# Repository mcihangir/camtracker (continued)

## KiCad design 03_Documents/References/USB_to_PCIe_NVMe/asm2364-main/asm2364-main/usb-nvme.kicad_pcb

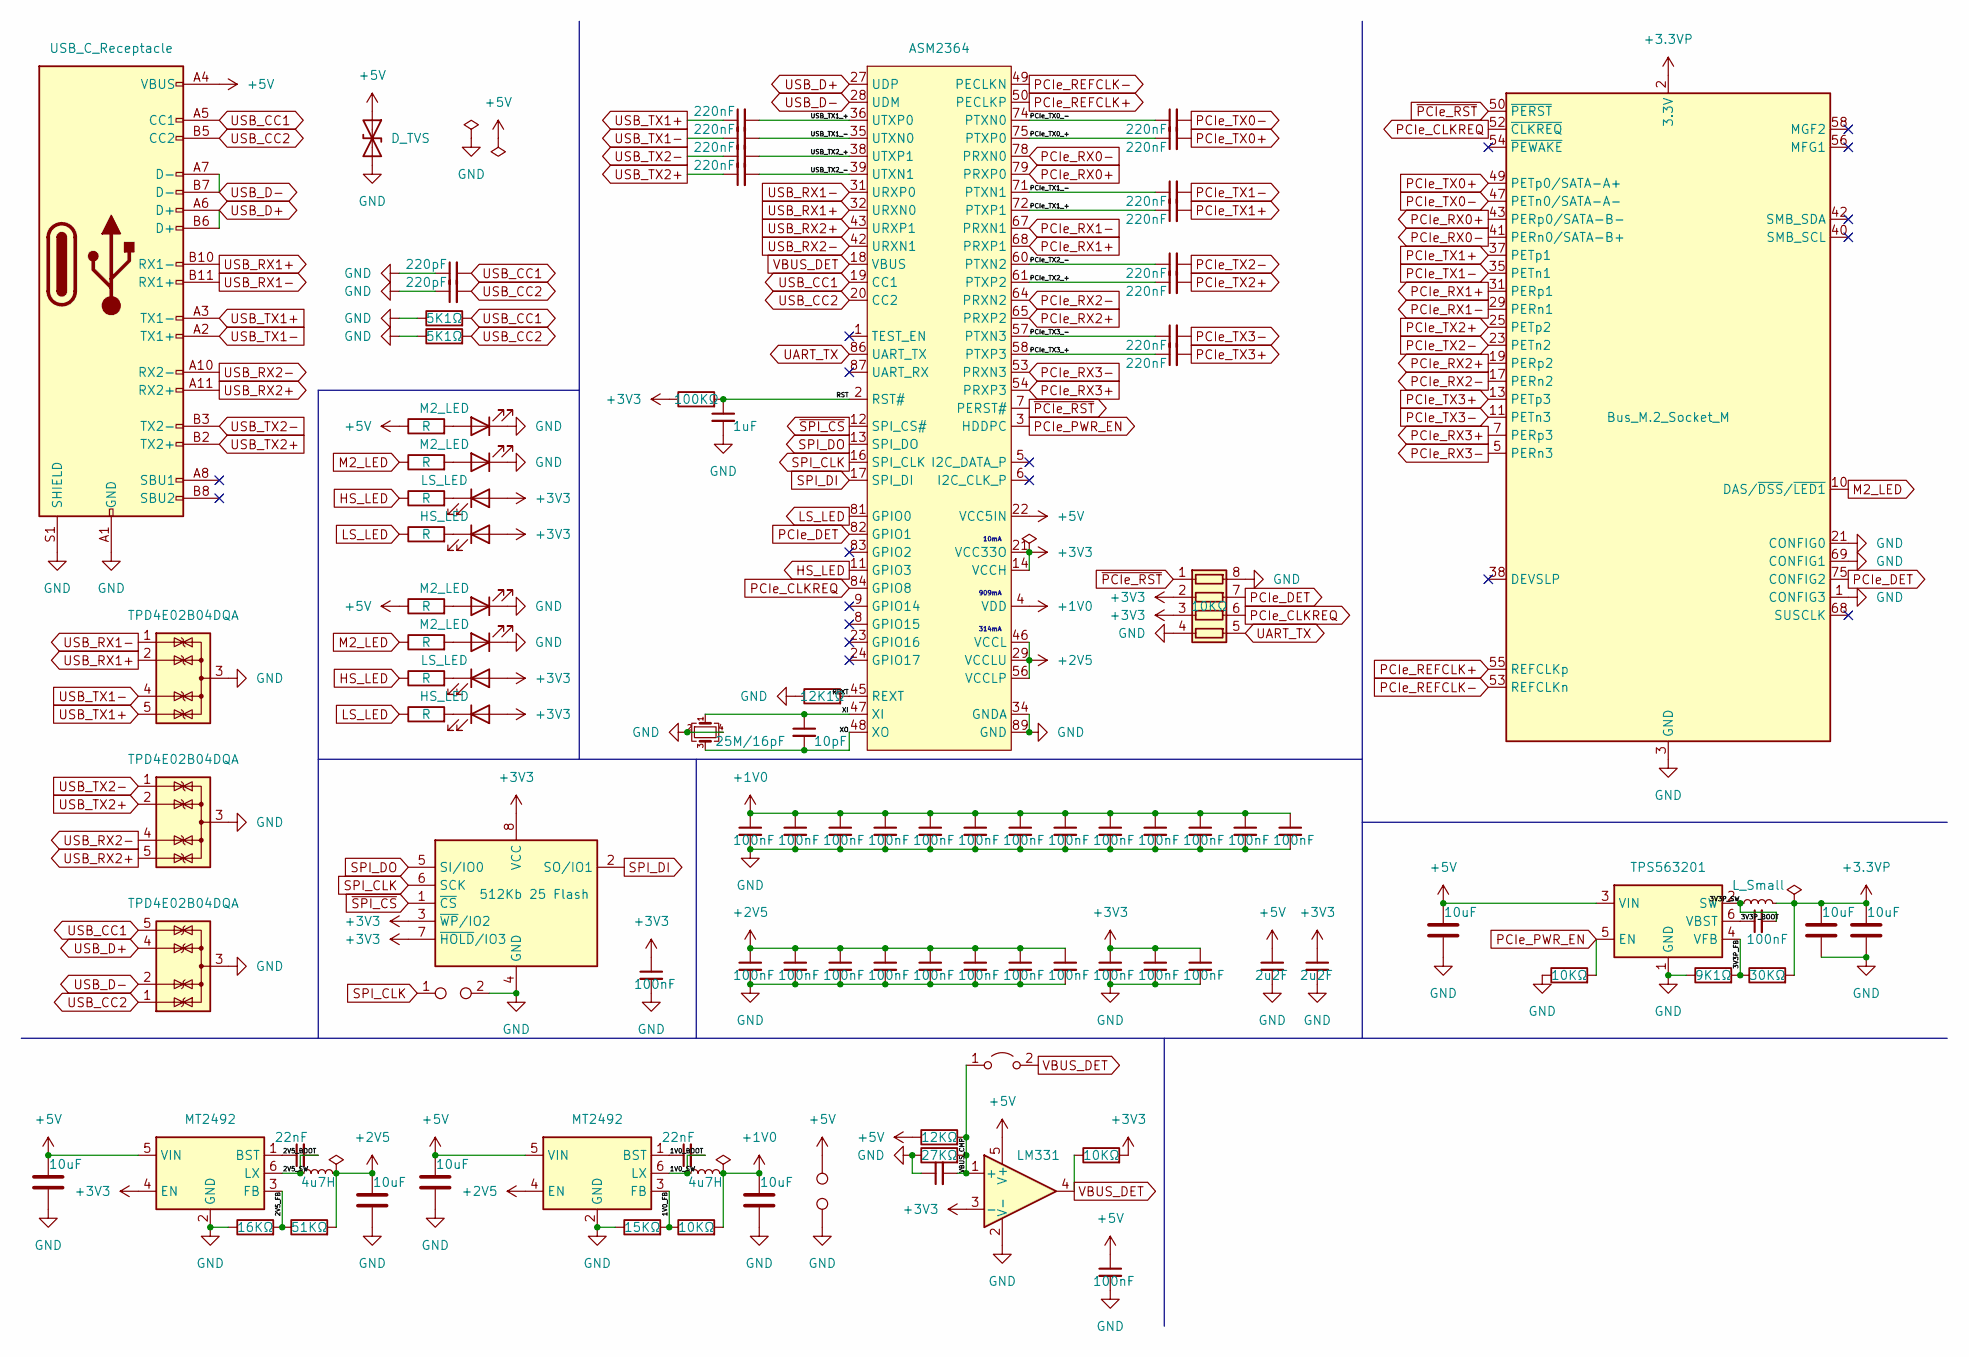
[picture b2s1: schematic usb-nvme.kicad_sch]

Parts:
C1, C2, C3, C4, C5, C6, C7, C8, C9, C11, C13, C14: 220nF; C_0201_0603Metric
C10, C12: 220pF; C_0201_0603Metric
C15: 1uF; C_0402_1005Metric
C16: 10pF; C_0201_0603Metric
C17, C18, C19, C20, C21, C22, C23, C24, C25, C26, C27, C28, C29, C30, C34, C35, C36, C37, C38, C39, C40, C41, C42, C43, C44, C47, C50, C55: 100nF; C_0201_0603Metric
C31, C32, C33, C51, C52, C53, C54: 10uF; C_0603_1608Metric
C45, C46: 2u2F; C_0402_1005Metric
C48, C49: 22nF; C_0201_0603Metric
D1: D_TVS; D_SOD-323
D2, D3, D6, D7: M2_LED; LED_0402_1005Metric
D4, D8: LS_LED; LED_0402_1005Metric
D5, D9: HS_LED; LED_0402_1005Metric
J1: USB_C_Receptacle; USB_C_Receptacle_GCT_USB4080-03-A
J2: Bus_M.2_Socket_M; M.2-M
JP1: Jumper; SolderJumper-2_1.2x0.6mm
L1: L_Small; L_Vishay_IHLP-1616
L2, L3: 4u7H; L_1008_2520Metric
R1, R2: 5K1Ω; R_0201_0603Metric
R3: 100KΩ; R_0201_0603Metric
R4, R5, R6, R7, R8, R9, R10, R12: R; R_0201_0603Metric
R11: 12K1Ω; R_0201_0603Metric
R13, R18, R22: 10KΩ; R_0201_0603Metric
R14: 9K1Ω; R_0201_0603Metric
R15: 30KΩ; R_0201_0603Metric
R16: 12KΩ; R_0201_0603Metric
R17: 27KΩ; R_0201_0603Metric
R19: 16KΩ; R_0201_0603Metric
R20: 51KΩ; R_0201_0603Metric
R21: 15KΩ; R_0201_0603Metric
RN1: 10KΩ; R_Array_Convex_4x0402
TP1: TestPoint_2Pole; R_0201_0603Metric
TP2, TP3: TestPoint; TestPoint_THTPad_2.0x2.0mm_Drill1.0mm
U1: ASM2364; QFN-88_EP_9.75x9.75_Pitch0.4mm_ThermalVias
U2, U3, U6: TPD4E02B04DQA; USON-10_2.5x1.0mm_P0.5mm
U4: 512Kb 25 Flash; DFN-8-1EP_3x2mm_P0.5mm_EP1.3x1.5mm
U5: TPS563201; SOT-23-6
U7, U8: MT2492; SOT-23-6
U9: LM331; SOT-353_SC-70-5
Y1: 25M/16pF; Crystal_SMD_2016-4Pin_2.0x1.6mm

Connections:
+1V0: C17.1, C18.1, C19.1, C20.1, C21.1, C22.1, C23.1, C24.1, C25.1, C26.1, C27.1, C28.1, C29.1, C54.1, L3.2, R22.2, U1.4 (VDD), U1.10 (VDD), U1.15 (VDD), U1.25 (VDD), U1.30 (VDD), U1.37 (VDD), U1.44 (VDD), U1.51 (VDD), U1.52 (VDD), U1.59 (VDD), U1.66 (VDD), U1.73 (VDD), U1.80 (VDD), U1.85 (VDD)
+2V5: C34.1, C35.1, C36.1, C37.1, C38.1, C39.1, C40.1, C41.1, C53.1, L2.2, R20.2, U1.29 (VCCLU), U1.33 (VCCLU), U1.41 (VCCLU), U1.46 (VCCL), U1.56 (VCCLP), U1.62 (VCCLP), U1.70 (VCCLP), U1.76 (VCCLP), U8.4 (EN)
+3.3VP: C32.1, C33.1, J2.0, J2.2 (3.3V), J2.4 (3.3V), J2.12 (3.3V), J2.14 (3.3V), J2.16 (3.3V), J2.18 (3.3V), J2.70 (3.3V), J2.72 (3.3V), J2.74 (3.3V), L1.2, R15.2
+3V3: C42.1, C43.1, C44.1, C46.1, C47.1, D4.2 (A), D5.2 (A), D8.2 (A), D9.2 (A), R3.1, R18.2, RN1.2 (R2.1), RN1.3 (R3.1), U1.14 (VCCH), U1.21 (VCC33O), U1.26 (VCCH), U1.88 (VCCH), U4.3 (~WP/IO2), U4.7 (~HOLD/IO3), U4.8 (VCC), U7.4 (EN), U9.3 (-)
+5V: C31.1, C45.1, C51.1, C52.1, C55.1, D1.1 (A1), J1.A4 (VBUS), J1.A9 (VBUS), J1.B4 (VBUS), J1.B9 (VBUS), J2.0, R4.1, R8.1, R16.1, TP2.1, U1.22 (VCC5IN), U5.3 (VIN), U7.5 (VIN), U8.5 (VIN), U9.5 (V+)
/1V0_BOOT: C49.1, U8.1 (BST)
/1V0_FB: R21.2, R22.1, U8.3 (FB)
/1V0_SW: C49.2, L3.1, U8.6 (LX)
/2V5_BOOT: C48.1, U7.1 (BST)
/2V5_FB: R19.2, R20.1, U7.3 (FB)
/2V5_SW: C48.2, L2.1, U7.6 (LX)
/3V3P_BOOT: C30.1, U5.6 (VBST)
/3V3P_FB: R14.2, R15.1, U5.4 (VFB)
/3V3P_SW: C30.2, L1.1, U5.2 (SW)
/PCIe_TX0_+: C4.1, U1.75 (PTXP0)
/PCIe_TX0_-: C2.1, U1.74 (PTXN0)
/PCIe_TX1_+: C8.1, U1.72 (PTXP1)
/PCIe_TX1_-: C7.1, U1.71 (PTXN1)
/PCIe_TX2_+: C11.1, U1.61 (PTXP2)
/PCIe_TX2_-: C9.1, U1.60 (PTXN2)
/PCIe_TX3_+: C14.1, U1.58 (PTXP3)
/PCIe_TX3_-: C13.1, U1.57 (PTXN3)
/REXT: R11.2, U1.45 (REXT)
/RST: C15.1, R3.2, U1.2 (RST#)
/USB_TX1_+: C1.2, U1.36 (UTXP0)
/USB_TX1_-: C3.2, U1.35 (UTXN0)
/USB_TX2_+: C5.2, U1.38 (UTXP1)
/USB_TX2_-: C6.2, U1.39 (UTXN1)
/VBUS_CMP: C50.2, JP1.1 (A), R16.2, R17.2, U9.1 (+)
/XI: C16.1, U1.47 (XI), Y1.1
/XO: C16.2, U1.48 (XO), Y1.3
GND: C10.1, C12.1, C15.2, C17.2, C18.2, C19.2, C20.2, C21.2, C22.2, C23.2, C24.2, C25.2, C26.2, C27.2, C28.2, C29.2, C31.2, C32.2, C33.2, C34.2, C35.2, C36.2, C37.2, C38.2, C39.2, C40.2, C41.2, C42.2, C43.2, C44.2, C45.2, C46.2, C47.2, C50.1, C51.2, C52.2, C53.2, C54.2, C55.2, D1.2 (A2), D2.1 (K), D3.1 (K), D6.1 (K), D7.1 (K), J1.A1 (GND), J1.A12 (GND), J1.B1 (GND), J1.B12 (GND), J1.S1 (SHIELD), J2.1 (CONFIG3), J2.3 (GND), J2.9 (GND), J2.15 (GND), J2.21 (CONFIG0), J2.27 (GND), J2.33 (GND), J2.39 (GND), J2.45 (GND), J2.51 (GND), J2.57 (GND), J2.69 (CONFIG1), J2.71 (GND), J2.73 (GND), R1.1, R2.1, R11.1, R13.1, R14.1, R17.1, R19.1, R21.1, RN1.4 (R4.1), RN1.8 (R1.2), TP1.2, TP3.1, U1.34 (GNDA), U1.40 (GNDA), U1.55 (GNDA), U1.63 (GNDA), U1.69 (GNDA), U1.77 (GNDA), U1.89 (GND), U2.3 (G), U2.8 (G), U3.3 (G), U3.8 (G), U4.4 (GND), U5.1 (GND), U6.3 (G), U6.8 (G), U7.2 (GND), U8.2 (GND), U9.2 (V-), Y1.2, Y1.4
HS_LED: R6.1, R10.1, U1.11 (GPIO3)
LS_LED: R7.1, R12.1, U1.81 (GPIO0)
M2_LED: J2.10 (DAS/~DSS/~LED1), R5.1, R9.1
unnamed: D2.2 (A), R4.2
unnamed: D3.2 (A), R5.2
unnamed: D4.1 (K), R6.2
unnamed: D5.1 (K), R7.2
unnamed: D6.2 (A), R8.2
unnamed: D7.2 (A), R9.2
unnamed: D8.1 (K), R10.2
unnamed: D9.1 (K), R12.2
PCIe_CLKREQ: J2.52 (~CLKREQ), RN1.6 (R3.2), U1.84 (GPIO8)
PCIe_DET: J2.75 (CONFIG2), RN1.7 (R2.2), U1.82 (GPIO1)
PCIe_PWR_EN: R13.2, U1.3 (HDDPC), U5.5 (EN)
PCIe_REFCLK+: J2.55 (REFCLKp), U1.50 (PECLKP)
PCIe_REFCLK-: J2.53 (REFCLKn), U1.49 (PECLKN)
PCIe_RX0+: J2.43 (PERp0/SATA-B-), U1.79 (PRXP0)
PCIe_RX0-: J2.41 (PERn0/SATA-B+), U1.78 (PRXN0)
PCIe_RX1+: J2.31 (PERp1), U1.68 (PRXP1)
PCIe_RX1-: J2.29 (PERn1), U1.67 (PRXN1)
PCIe_RX2+: J2.19 (PERp2), U1.65 (PRXP2)
PCIe_RX2-: J2.17 (PERn2), U1.64 (PRXN2)
PCIe_RX3+: J2.7 (PERp3), U1.54 (PRXP3)
PCIe_RX3-: J2.5 (PERn3), U1.53 (PRXN3)
PCIe_TX0+: C4.2, J2.49 (PETp0/SATA-A+)
PCIe_TX0-: C2.2, J2.47 (PETn0/SATA-A-)
PCIe_TX1+: C8.2, J2.37 (PETp1)
PCIe_TX1-: C7.2, J2.35 (PETn1)
PCIe_TX2+: C11.2, J2.25 (PETp2)
PCIe_TX2-: C9.2, J2.23 (PETn2)
PCIe_TX3+: C14.2, J2.13 (PETp3)
PCIe_TX3-: C13.2, J2.11 (PETn3)
SPI_CLK: TP1.1, U1.16 (SPI_CLK), U4.6 (SCK)
SPI_DI: U1.17 (SPI_DI), U4.2 (SO/IO1)
SPI_DO: U1.13 (SPI_DO), U4.5 (SI/IO0)
UART_TX: RN1.5 (R4.2), U1.86 (UART_TX)
USB_CC1: C10.2, J1.A5 (CC1), R1.2, U1.19 (CC1), U6.5 (IO4), U6.6 (IO4)
USB_CC2: C12.2, J1.B5 (CC2), R2.2, U1.20 (CC2), U6.1 (IO1), U6.10 (IO1)
USB_D+: J1.A6 (D+), J1.B6 (D+), U1.27 (UDP), U6.4 (IO3), U6.7 (IO3)
USB_D-: J1.A7 (D-), J1.B7 (D-), U1.28 (UDM), U6.2 (IO2), U6.9 (IO2)
USB_RX1+: J1.B10 (RX1-), U1.32 (URXN0), U2.2 (IO2), U2.9 (IO2)
USB_RX1-: J1.B11 (RX1+), U1.31 (URXP0), U2.1 (IO1), U2.10 (IO1)
USB_RX2+: J1.A11 (RX2+), U1.43 (URXP1), U3.5 (IO4), U3.6 (IO4)
USB_RX2-: J1.A10 (RX2-), U1.42 (URXN1), U3.4 (IO3), U3.7 (IO3)
USB_TX1+: C1.1, J1.A3 (TX1-), U2.5 (IO4), U2.6 (IO4)
USB_TX1-: C3.1, J1.A2 (TX1+), U2.4 (IO3), U2.7 (IO3)
USB_TX2+: C6.1, J1.B2 (TX2+), U3.2 (IO2), U3.9 (IO2)
USB_TX2-: C5.1, J1.B3 (TX2-), U3.1 (IO1), U3.10 (IO1)
VBUS_DET: JP1.2 (B), R18.1, U1.18 (VBUS), U9.4
~PCIe_RST: J2.50 (~PERST), RN1.1 (R1.1), U1.7 (PERST#)
~SPI_CS: U1.12 (SPI_CS#), U4.1 (~CS)

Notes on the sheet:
314mA
10mA
909mA

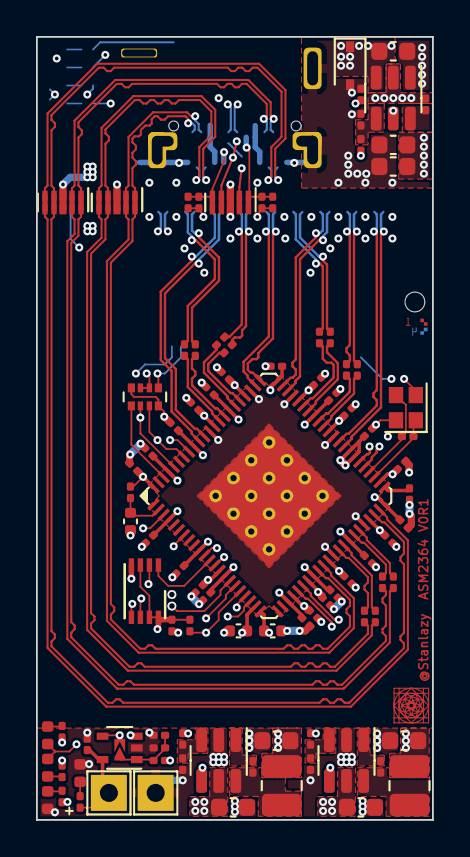
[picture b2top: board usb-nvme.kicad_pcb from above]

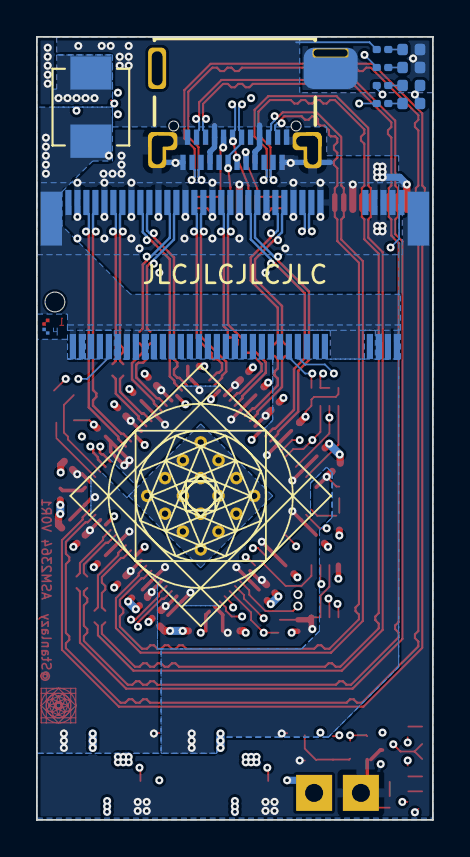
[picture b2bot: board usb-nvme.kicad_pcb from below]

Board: 4 copper layers, 22.0 x 43.5 mm, 106 parts (11 on the bottom side), 83 nets.

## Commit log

2025-10-18 feat: first commit with 5V DCDC
2025-10-29 feat: Completed Placement v1 in Layout
2025-10-30 feat(layout): Completed Placement v2
    Includes:
    - 3V8 DC-DC converter moved to the top layer
    - SIM and SD card positions rearranged
2025-10-30 feat(layout): Routed DP traces
    Includes:
    - Routed DP Camera/USB/PCIe
    - Routed SIM/SD
    - Routed ASM
    - Routed RP
2025-11-01 feat(layout): Routed almost all traces
2025-11-02 feat(layout): Completed routing of all traces but with Errors DRCs
2025-11-03 feat(layout): Resolved all DRC Errors
2025-11-05 feat(layout): Placed all references
2025-11-09 feat(layout): matched DP trace lengths for signal integrity
2025-11-10 feat(layout): Adjusted mounting holes and board edge copper
2025-11-14 feat(layout): Completed v1.0 with old Camera Connector
2025-11-16 feat(layout): Completed Layout Design with new Camera Connectors
2025-11-17 feat(PCB): Finalized design and generated Gerber files and BOM
2025-12-01 feat(PCB): Added TE Connectivity connectors except the SD connector
2025-12-15 feat(PCB): Cam Connectors have been changed with 2x10P
2025-12-18 feat(PCB): DC input Capacitor has been changed
2025-12-19 feat(PCB): Added GPIO IN to SC206E from the MCU
2025-12-22 feat(PCB): finalize PCB design and generate BOM/Gerbers
2025-12-24 feat(PCB): Generated Pick and Placement file and pilot the Schematic
2025-12-26 feat(PCB): Updated NVME USB EN logic, turn-off the NVME 3V3 and 1V05 by EN pin
2026-04-01 Added To Be Fixed and Bring up Test Document
